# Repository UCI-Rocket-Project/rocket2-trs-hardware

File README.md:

## 🛰️ Telemetry Radio System (TRS) 🛰️
Click [here](https://uci-rocket-project.github.io/rocket2-trs-hardware/) TRS documentation

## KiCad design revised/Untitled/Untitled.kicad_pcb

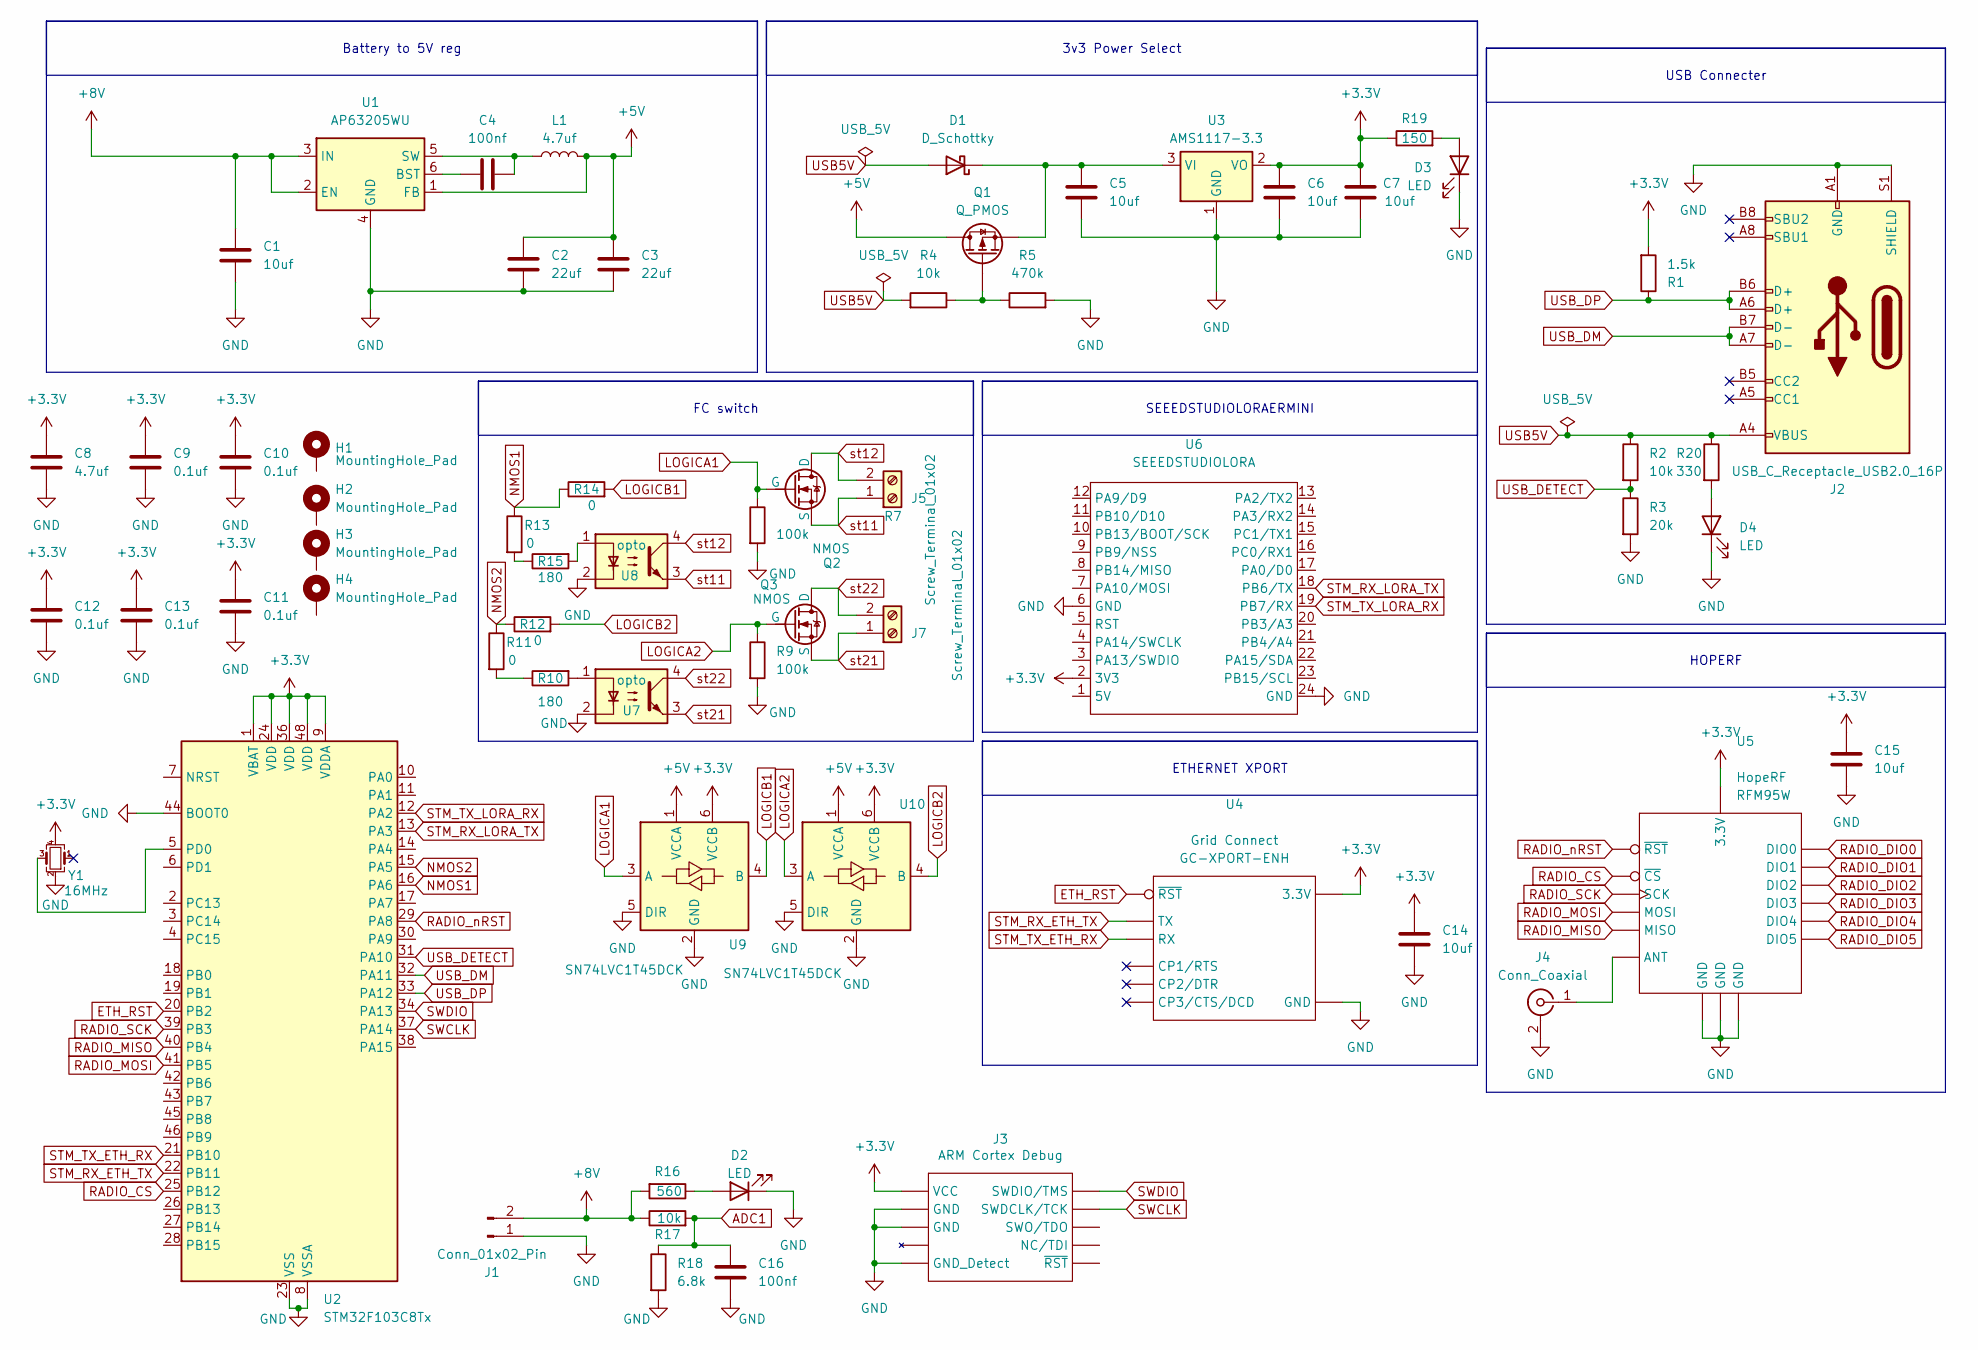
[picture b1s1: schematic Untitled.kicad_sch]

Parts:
C1, C5, C6, C7, C14, C15: 10uf; C_0603_1608Metric_Pad1.08x0.95mm_HandSolder
C2, C3: 22uf; C_0603_1608Metric_Pad1.08x0.95mm_HandSolder
C4, C16: 100nf; C_0603_1608Metric_Pad1.08x0.95mm_HandSolder
C8: 4.7uf; C_0603_1608Metric_Pad1.08x0.95mm_HandSolder
C9, C10, C11, C12, C13: 0.1uf; C_0603_1608Metric_Pad1.08x0.95mm_HandSolder
D1: D_Schottky; D_SMA_Handsoldering
D2, D3, D4: LED; R_0603_1608Metric_Pad0.98x0.95mm_HandSolder
H1, H2, H3, H4: MountingHole_Pad; MountingHole_4.3mm_M4_DIN965_Pad_TopBottom
J1: Conn_01x02_Pin; AMASS_XT60PW-M_1x02_P7.20mm_Horizontal
J2: USB_C_Receptacle_USB2.0_16P; USB_C_Receptacle_GCT_USB4105-xx-A_16P_TopMnt_Horizontal
J3: ARM Cortex Debug; PinHeader_2x05_P1.27mm_Vertical_SMD
J4: Conn_Coaxial; CONN_73391-0070_MOL
J5, J7: Screw_Terminal_01x02; TerminalBlock_Phoenix_MKDS-1,5-2-5.08_1x02_P5.08mm_Horizont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
L1: 4.7uf; C_0603_1608Metric_Pad1.08x0.95mm_HandSolder
Q1: Q_PMOS; TSOT-23_HandSoldering
Q2, Q3: NMOS; SOT-23-6
R1: 1.5k; R_0603_1608Metric_Pad0.98x0.95mm_HandSolder
R2, R4, R17: 10k; R_0603_1608Metric_Pad0.98x0.95mm_HandSolder
R3: 20k; R_0603_1608Metric_Pad0.98x0.95mm_HandSolder
R5: 470k; R_0603_1608Metric_Pad0.98x0.95mm_HandSolder
R7, R9: 100k; R_0603_1608Metric_Pad0.98x0.95mm_HandSolder
R10, R15: 180; R_0603_1608Metric_Pad0.98x0.95mm_HandSolder
R11, R12, R13, R14: 0; R_0603_1608Metric_Pad0.98x0.95mm_HandSolder
R16: 560; R_0603_1608Metric_Pad0.98x0.95mm_HandSolder
R18: 6.8k; R_0603_1608Metric_Pad0.98x0.95mm_HandSolder
R19: 150; R_0603_1608Metric_Pad0.98x0.95mm_HandSolder
R20: 330; R_0603_1608Metric_Pad0.98x0.95mm_HandSolder
U1: AP63205WU; TSOT-23-6
U2: STM32F103C8Tx; LQFP-48_7x7mm_P0.5mm
U3: AMS1117-3.3; SOT-223-3_TabPin2
U4: GC-XPORT; Part # GC-XPORT-ENH
U5: RFM95W; Part # RFM95W
U6: SEEEDSTUDIOLORA; Untitled
U7, U8: opto; optocoupler
U9, U10: SN74LVC1T45DCK; SOT-363_SC-70-6
Y1: 16MHz; Crystal_SMD_2016-4Pin_2.0x1.6mm; Part # ECS-1633-160-BN-TR

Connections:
+3.3V: C6.1, C7.1, C8.1, C9.1, C10.1, C11.1, C12.1, C13.1, C14.1, C15.1, J3.1 (VCC), R1.2, R19.1, U2.1 (VBAT), U2.9 (VDDA), U2.24 (VDD), U2.36 (VDD), U2.48 (VDD), U3.2 (VO), U4.2 (3.3V), U5.13 (3.3V), U6.2 (3V3), U9.6 (VCCB), U10.6 (VCCB), Y1.4
+5V: C2.1, C3.1, L1.2, Q1.3 (D), U1.1 (FB), U9.1 (VCCA), U10.1 (VCCA)
+8V: C1.1, J1.2, R16.2, R17.1, U1.2 (EN), U1.3 (IN)
ADC1: C16.1, R17.2, R18.1
ETH_RST: U2.20 (PB2), U4.3 (~RST)
GND: C1.2, C2.2, C3.2, C5.2, C6.2, C7.2, C8.2, C9.2, C10.2, C11.2, C12.2, C13.2, C14.2, C15.2, C16.2, D2.1 (K), D3.1 (K), D4.1 (K), J1.1, J2.A1 (GND), J2.A12 (GND), J2.B1 (GND), J2.B12 (GND), J2.S1 (SHIELD), J3.3 (GND), J3.5 (GND), J3.9 (GND_Detect), J4.2 (Ext), R3.2, R5.2, R7.2, R9.2, R18.2, U1.4 (GND), U2.8 (VSSA), U2.23 (VSS), U2.35 (VSS), U2.44 (BOOT0), U2.47 (VSS), U3.1 (GND), U4.1 (GND), U5.1 (GND), U5.8 (GND), U5.10 (GND), U6.6 (GND), U6.24 (GND), U7.2, U8.2, U9.2 (GND), U9.5 (DIR), U10.2 (GND), U10.5 (DIR), Y1.2
LOGICA1: Q2.3 (G), R7.1, U9.3 (A)
LOGICA2: Q3.3 (G), R9.1, U10.3 (A)
LOGICB1: R14.2, U9.4 (B)
LOGICB2: R12.2, U10.4 (B)
NMOS1: R13.1, R14.1, U2.16 (PA6)
NMOS2: R11.1, R12.1, U2.15 (PA5)
unnamed: C5.1, D1.1 (K), Q1.2 (S), U3.3 (VI)
unnamed: D2.2 (A), R16.1
unnamed: D3.2 (A), R19.2
unnamed: D4.2 (A), R20.2
unnamed: J4.1 (In), U5.9 (ANT)
unnamed: Q1.1 (G), R4.1, R5.1
unnamed: R10.1, R11.2
unnamed: R10.2, U7.1
unnamed: R13.2, R15.1
unnamed: R15.2, U8.1
unnamed: C4.2, U1.6 (BST)
unnamed: C4.1, L1.1, U1.5 (SW)
unnamed: U2.5 (PD0), Y1.3
RADIO_CS: U2.25 (PB12), U5.5 (~CS)
RADIO_DIO0: U5.14 (DIO0)
RADIO_DIO1: U5.15 (DIO1)
RADIO_DIO2: U5.16 (DIO2)
RADIO_DIO3: U5.11 (DIO3)
RADIO_DIO4: U5.12 (DIO4)
RADIO_DIO5: U5.7 (DIO5)
RADIO_MISO: U2.40 (PB4), U5.2 (MISO)
RADIO_MOSI: U2.41 (PB5), U5.3 (MOSI)
RADIO_SCK: U2.39 (PB3), U5.4 (SCK)
RADIO_nRST: U2.29 (PA8), U5.6 (~RST)
STM_RX_ETH_TX: U2.22 (PB11), U4.4 (TX)
STM_RX_LORA_TX: U2.13 (PA3), U6.18 (PB6/TX)
STM_TX_ETH_RX: U2.21 (PB10), U4.5 (RX)
STM_TX_LORA_RX: U2.12 (PA2), U6.19 (PB7/RX)
SWCLK: J3.4 (SWDCLK/TCK), U2.37 (PA14)
SWDIO: J3.2 (SWDIO/TMS), U2.34 (PA13)
USB5V: D1.2 (A), J2.A4 (VBUS), J2.A9 (VBUS), J2.B4 (VBUS), J2.B9 (VBUS), R2.1, R4.2, R20.1
USB_DETECT: R2.2, R3.1, U2.31 (PA10)
USB_DM: J2.A7 (D-), J2.B7 (D-), U2.32 (PA11)
USB_DP: J2.A6 (D+), J2.B6 (D+), R1.1, U2.33 (PA12)
st11: J5.1, Q2.4 (S), U8.3
st12: J5.2, Q2.1 (D), U8.4
st21: J7.1, Q3.4 (S), U7.3
st22: J7.2, Q3.1 (D), U7.4

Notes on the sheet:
FC switch
3v3 Power Select
HOPERF
USB Connecter
ETHERNET XPORT
SEEEDSTUDIOLORAERMINI
Battery to 5V reg

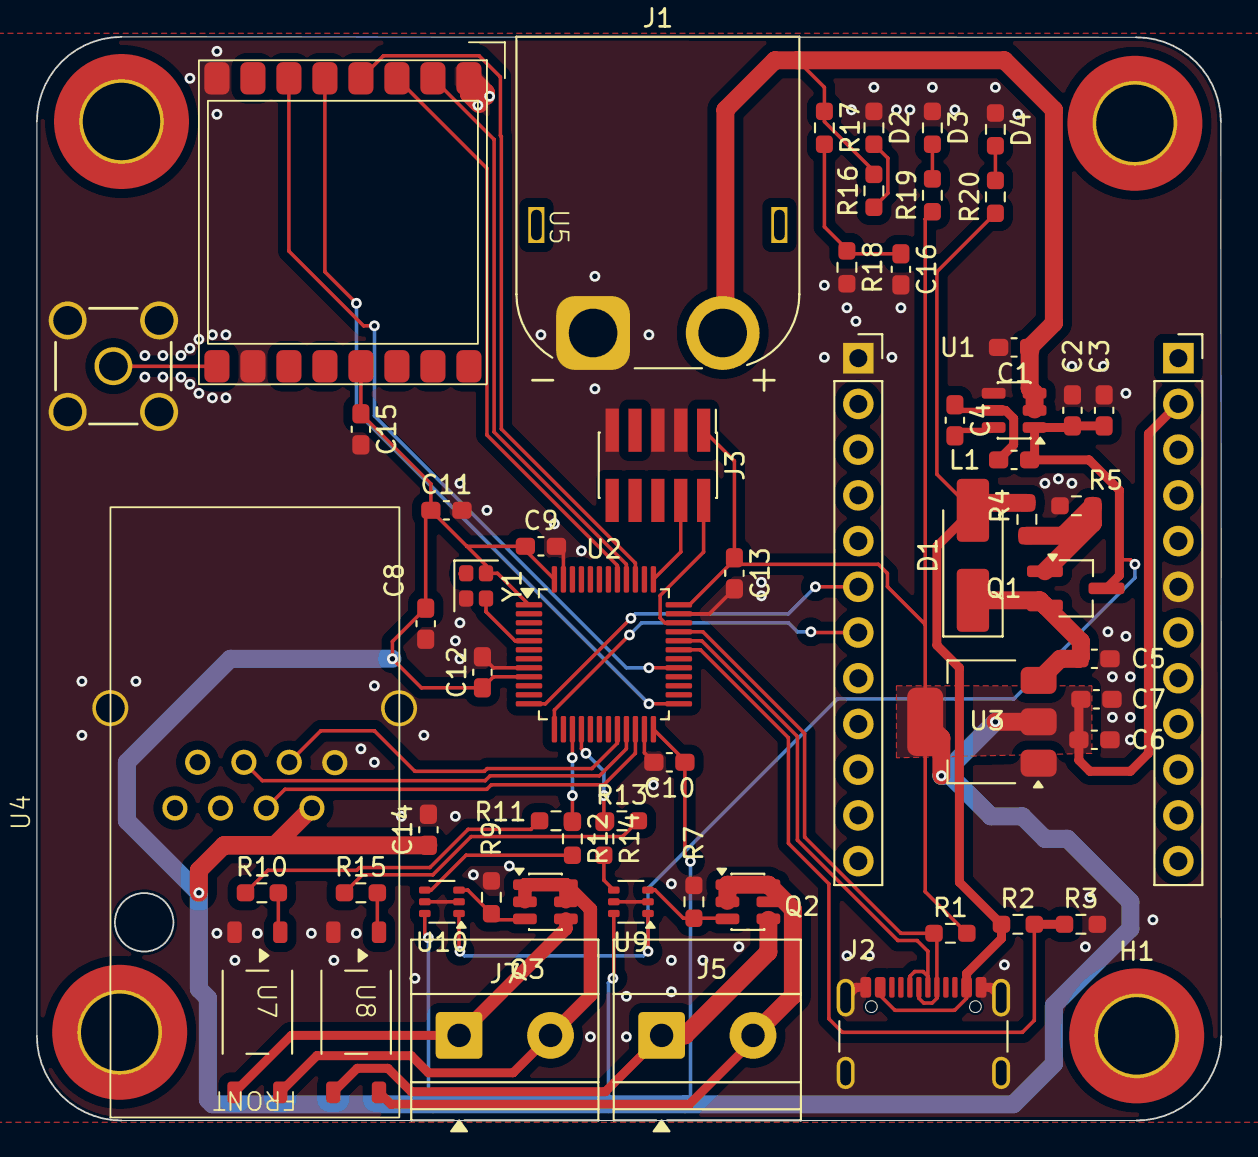
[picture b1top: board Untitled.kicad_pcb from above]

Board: 2 copper layers, 65.8 x 60.2 mm, 63 parts (0 on the bottom side), 44 nets.

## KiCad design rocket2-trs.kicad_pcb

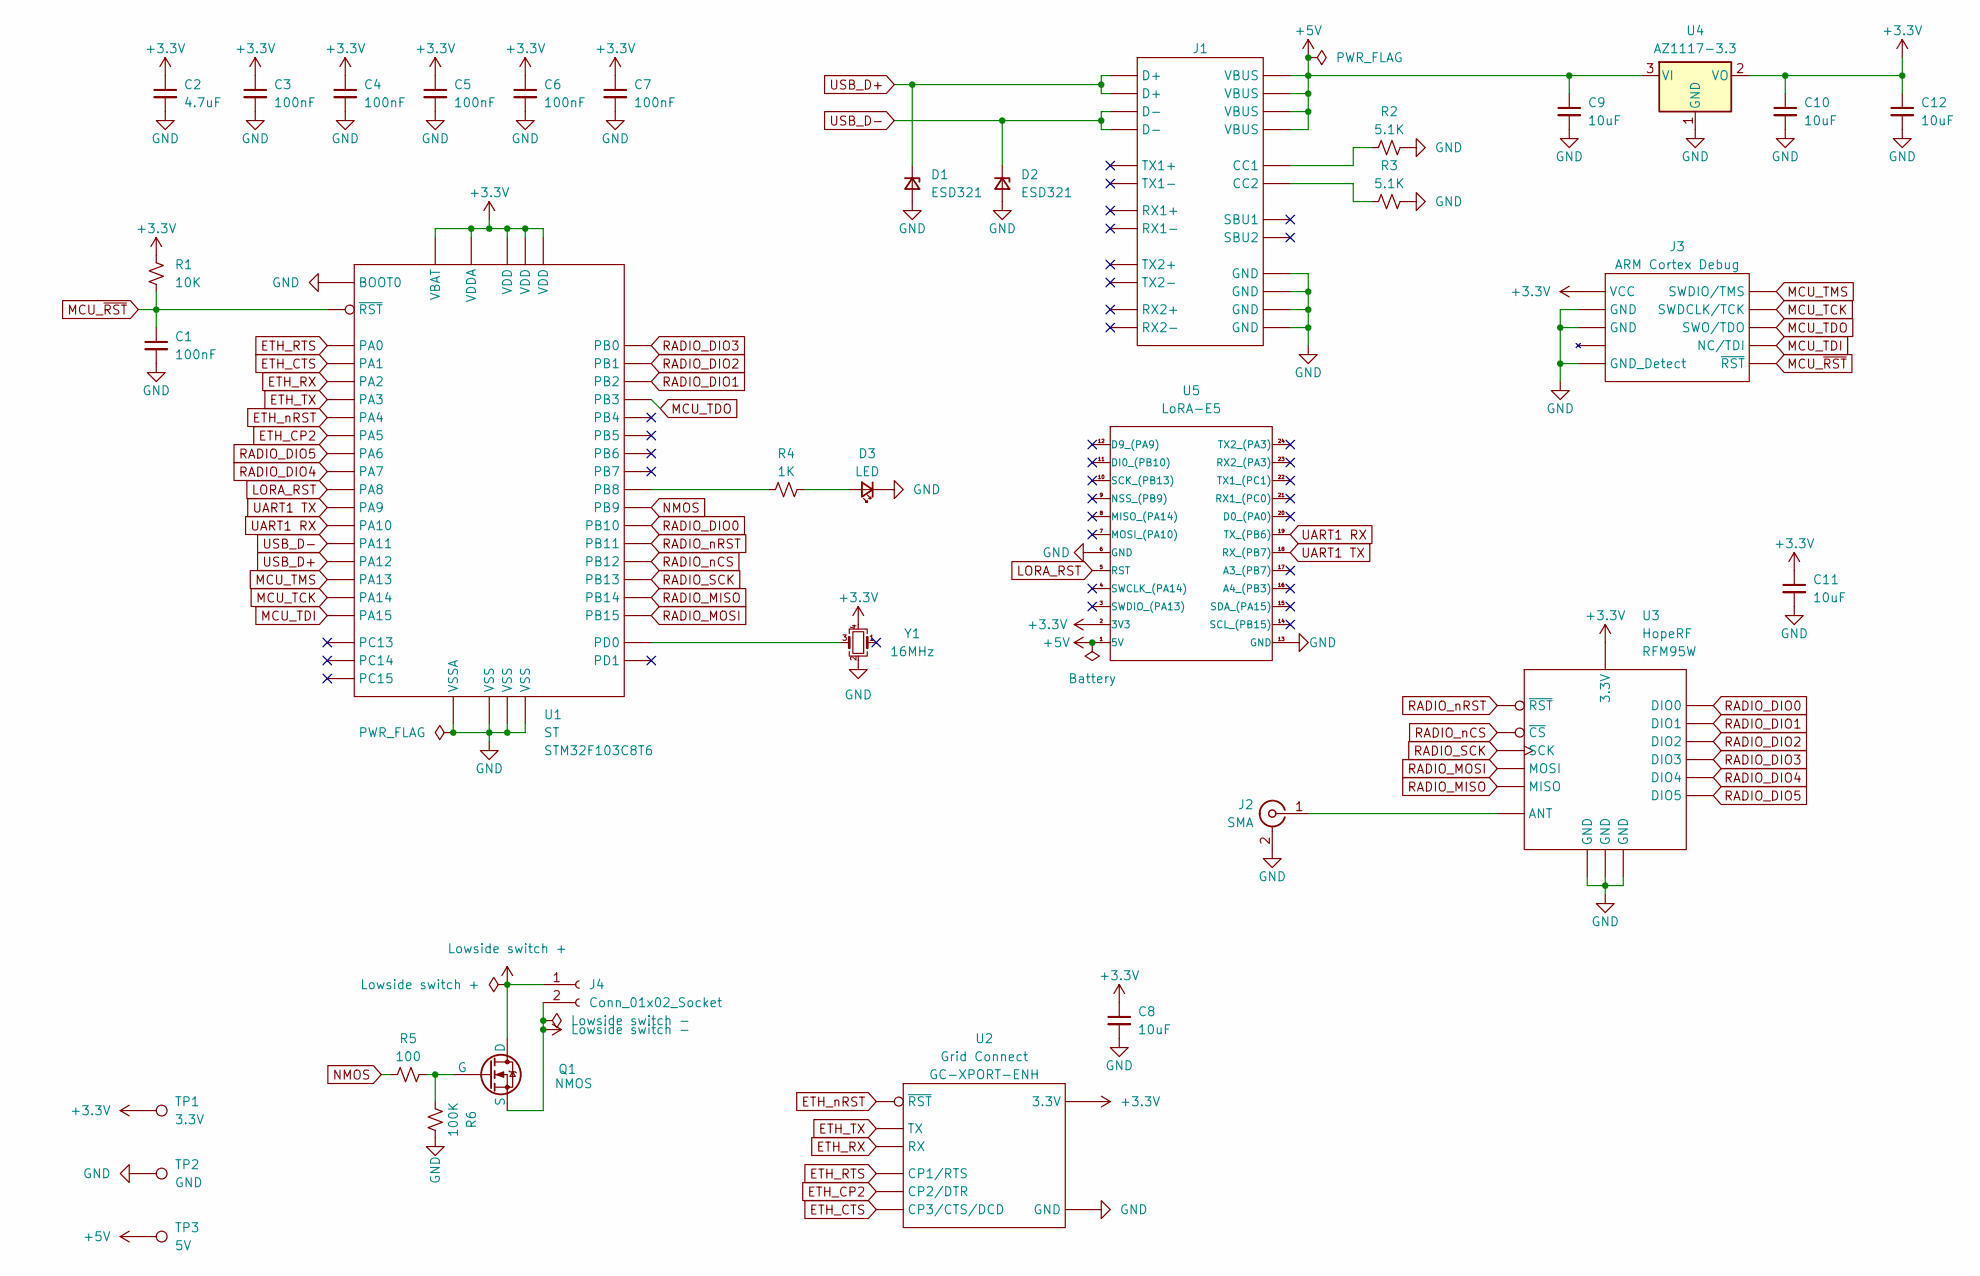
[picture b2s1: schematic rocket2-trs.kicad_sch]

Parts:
C1, C3, C4, C5, C6, C7: 100nF; C_0603_1608Metric; Part # Generic 0603 100nF 6.3V X7R MLCC
C2: 4.7uF; C_0603_1608Metric; Part # Generic 0603 4.7uF 6.3V X7R MLCC
C8, C9, C10, C11, C12: 10uF; C_0603_1608Metric; Part # Generic 0603 10uF 6.3V X7R MLCC
D1, D2: ESD321; D_0402_1005Metric; Part # ESD321DPYR
D3: LED; D_0603_1608Metric; Part # Generic 0603 Red LED
J1: USB_C_Receptacle_GCT_USB4105-xx-A_16P_TopMnt_Horizontal; Part # USB4105-GF-A
J2: SMA; SMA_Molex_73251-2200_Horizontal; Part # 732512200
J3: ARM Cortex Debug; PinHeader_2x05_P1.27mm_Vertical_SMD; Part # Generic 1.27mm 2x5 Pin Header
J4: Conn_01x02_Socket; PinSocket_1x02_P1.27mm_Vertical
Q1: NMOS; SOT-23
R1: 10K; R_0603_1608Metric; Part # Generic 0603 10K 1% Resistor
R2, R3: 5.1K; R_0603_1608Metric; Part # Generic 0603 5.1K 1% Resistor
R4: 1K; R_0603_1608Metric; Part # Generic 0603 1K 1% Resistor
R5: 100; R_0603_1608Metric; Part # Generic 0603 5.1K 1% Resistor
R6: 100K; R_0603_1608Metric; Part # Generic 0603 5.1K 1% Resistor
TP1: 3.3V; TestPoint_Pad_D1.0mm
TP2: GND; TestPoint_Pad_D1.0mm
TP3: 5V; TestPoint_Pad_D1.0mm
U1: LQFP-48_7x7mm_P0.5mm; Part # STM32F103C8T6
U2: GC-XPORT; Part # GC-XPORT-ENH
U3: RFM95W; Part # RFM95W
U4: AZ1117-3.3; SOT-223-3_TabPin2; Part # AZ1117IH-3.3TRG1
U5: LoRA-E5; LoRa - E5
Y1: 16MHz; Crystal_SMD_2520-4Pin_2.5x2.0mm; Part # ECS-2520MV-160-CN

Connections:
+3.3V: C2.1, C3.1, C4.1, C5.1, C6.1, C7.1, C8.1, C10.1, C11.1, C12.1, J3.1 (VCC), R1.1, TP1.1, U1.1 (VBAT), U1.9 (VDDA), U1.24 (VDD), U1.36 (VDD), U1.48 (VDD), U2.2 (3.3V), U3.13 (3.3V), U4.2 (VO), U5.2 (3V3), Y1.4
+5V: C9.1, J1.A4 (VBUS), J1.A9 (VBUS), J1.B4 (VBUS), J1.B9 (VBUS), TP3.1, U4.3 (VI), U5.1 (5V)
ETH_CP2: U1.15 (PA5), U2.7 (CP2/DTR)
ETH_CTS: U1.11 (PA1), U2.8 (CP3/CTS/DCD)
ETH_RTS: U1.10 (PA0), U2.6 (CP1/RTS)
ETH_RX: U1.12 (PA2), U2.5 (RX)
ETH_TX: U1.13 (PA3), U2.4 (TX)
ETH_nRST: U1.14 (PA4), U2.3 (~RST)
GND: C1.2, C2.2, C3.2, C4.2, C5.2, C6.2, C7.2, C8.2, C9.2, C10.2, C11.2, C12.2, D1.2 (A), D2.2 (A), D3.1 (K), J1.A1 (GND), J1.A12 (GND), J1.B1 (GND), J1.B12 (GND), J2.2 (Ext), J3.3 (GND), J3.5 (GND), J3.9 (GND_Detect), R2.2, R3.2, R6.2, TP2.1, U1.8 (VSSA), U1.23 (VSS), U1.35 (VSS), U1.44 (BOOT0), U1.47 (VSS), U2.1 (GND), U3.1 (GND), U3.8 (GND), U3.10 (GND), U4.1 (GND), U5.6 (GND), U5.13 (GND), Y1.2
LORA_RST: U1.29 (PA8), U5.5 (RST)
Lowside switch +: J4.1, Q1.3 (D)
Lowside switch -: J4.2, Q1.2 (S)
MCU_TCK: J3.4 (SWDCLK/TCK), U1.37 (PA14)
MCU_TDI: J3.8 (NC/TDI), U1.38 (PA15)
MCU_TDO: J3.6 (SWO/TDO), U1.39 (PB3)
MCU_TMS: J3.2 (SWDIO/TMS), U1.34 (PA13)
MCU_~RST: C1.1, J3.10 (~RST), R1.2, U1.7 (~RST)
NMOS: R5.1, U1.46 (PB9)
unnamed: D3.2 (A), R4.2
unnamed: J1.A5 (CC1), R2.1
unnamed: J1.B5 (CC2), R3.1
unnamed: J2.1 (In), U3.9 (ANT)
unnamed: Q1.1 (G), R5.2, R6.1
unnamed: R4.1, U1.45 (PB8)
unnamed: U1.5 (PD0), Y1.3
RADIO_DIO0: U1.21 (PB10), U3.14 (DIO0)
RADIO_DIO1: U1.20 (PB2), U3.15 (DIO1)
RADIO_DIO2: U1.19 (PB1), U3.16 (DIO2)
RADIO_DIO3: U1.18 (PB0), U3.11 (DIO3)
RADIO_DIO4: U1.17 (PA7), U3.12 (DIO4)
RADIO_DIO5: U1.16 (PA6), U3.7 (DIO5)
RADIO_MISO: U1.27 (PB14), U3.2 (MISO)
RADIO_MOSI: U1.28 (PB15), U3.3 (MOSI)
RADIO_SCK: U1.26 (PB13), U3.4 (SCK)
RADIO_nCS: U1.25 (PB12), U3.5 (~CS)
RADIO_nRST: U1.22 (PB11), U3.6 (~RST)
UART1 RX: U1.31 (PA10), U5.19 (TX_(PB6))
UART1 TX: U1.30 (PA9), U5.18 (RX_(PB7))
USB_D+: D1.1 (K), J1.A6 (D+), J1.B6 (D+), U1.33 (PA12)
USB_D-: D2.1 (K), J1.A7 (D-), J1.B7 (D-), U1.32 (PA11)

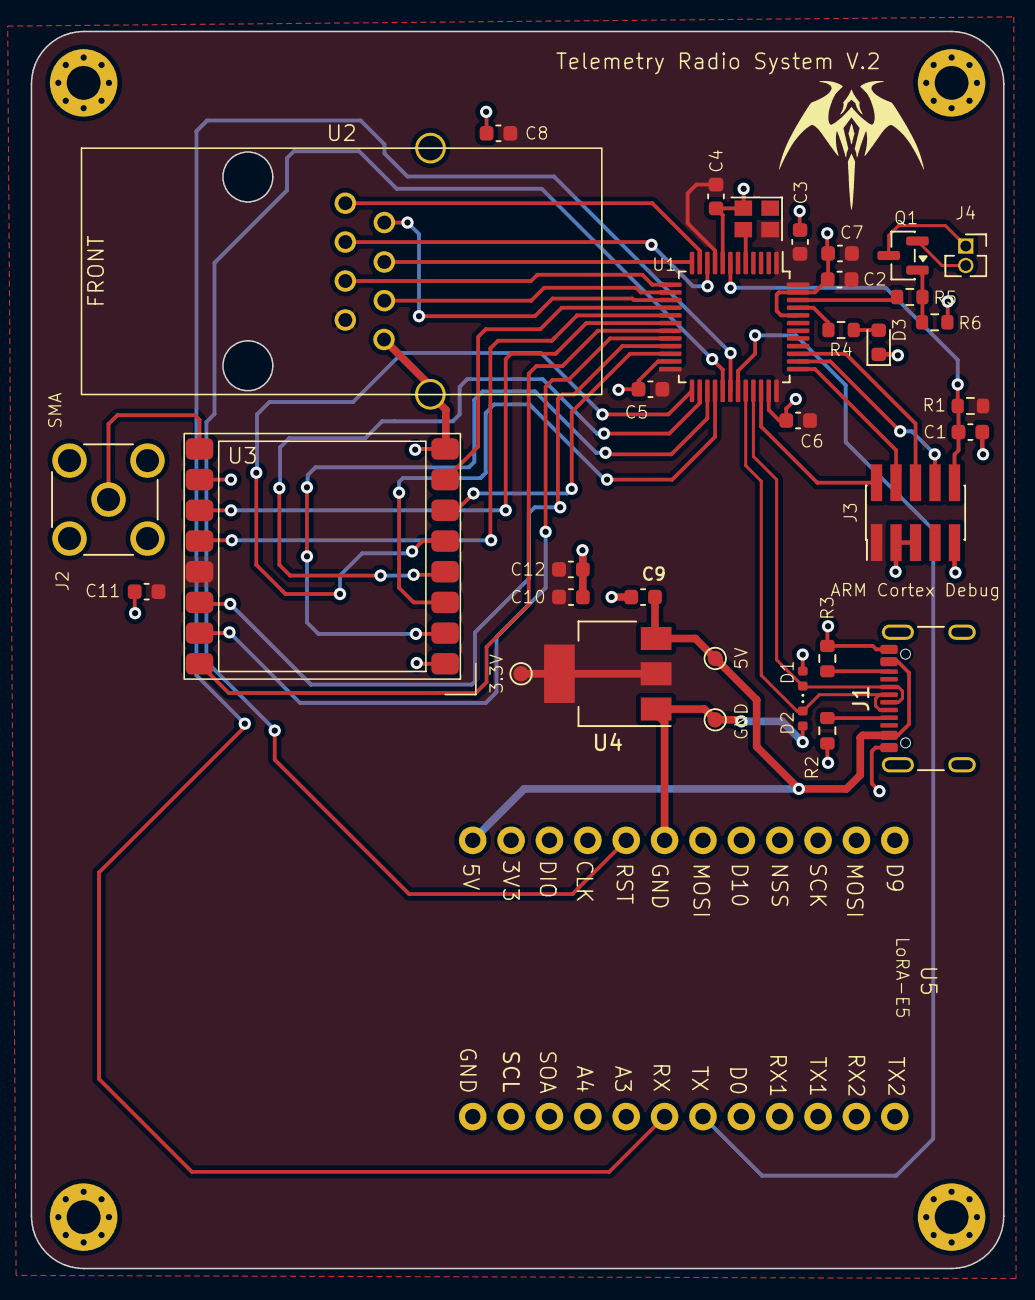
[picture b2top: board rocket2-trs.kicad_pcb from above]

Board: 2 copper layers, 63.4 x 80.6 mm, 35 parts (0 on the bottom side), 40 nets.

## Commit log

2024-01-25 Add schematic
2024-01-26 Add test points
2024-01-26 Add PCB
2024-01-26 Add LED
2025-11-15 TRS Update 1
2025-11-19 TRS 1
2025-11-21 TRS Update 2 - need feedback on LoRA
2025-11-21 bleh
2025-12-15 trs update 12/14/2025
2026-01-15 TRS fixed
2026-01-16 added test points, removed connectors
2026-01-21 adding nmos
2026-01-22 added nmos and fixed rx tx
2026-01-22 fixing
2026-01-23 Fixed board size and removed eth from lora
2026-01-26 revised
2026-01-26 layout revised
2026-01-26 signal routing start
2026-01-27 optocouplers added
2026-01-29 cleaned up layout and board shape finalized
2026-01-31 prereview board
2026-02-01 TRS production ready
2026-04-21 MKDOCS FOR TRS
2026-04-21 MK DOCS FOR TRS HARDWARE
2026-04-21 commit mkdocs
2026-04-25 Updated TRS docs
2026-04-25 Deployed 48f9a95 with MkDocs version: 1.6.1
2026-04-29 Reformatted repo file structure
2026-04-29 Add TRS documentation link to README
2026-05-06 Added sys diagram, circuit photos, tightened descriptions, added master hardware page and added trs-gnd hardware page
